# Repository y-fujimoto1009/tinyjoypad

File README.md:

# tinyjoypad キット

tinyjoypad キットは、attiny85を使ったゲーム機を作成するためのキットです。<br>
tinyjoypadプロジェクトは
[こちら](https://www.tinyjoypad.com/tinyjoypad_attiny85) 

## 内容物

- 基板 x 1
- LED x 1
- ピンヘッダー（2×3） x 1
- スライドスイッチ x 1
- attiny85 x 1
- 丸ピンICソケット (8P) x 1
- 抵抗（10kΩ） x 2
- 抵抗（22kΩ） x 2
- 抵抗（33kΩ） x 2
- 抵抗（91kΩ） x 2
- タクトスイッチ x 5
- スイッチキャップ x 5
- ブザー x 1
- ボタン電池ホルダー x 1
- 0.96インチ有機ELディスプレイ(OLED)  x 1
- USBasp AVRライタ x 1(スイッチサイエンスで購入した方のみ）

## 自分で用意する必要があるもの
最近は100均などでも手に入りますね。
- はんだごて、はんだ
- マスキングテープ
- ニッパー
- ボタン電池（CR2032）

## 作成手順
1. 抵抗を基板に書かれた場所に配置します。間違えないようにしましょう。向きは関係ありません。<br>
はんだで接続できたら、余った足はニッパーでカットしてOKです。
どの抵抗かわからなくなっても落ち着いてカラーコードを確認すれば大丈夫です。<br>

<br>
 10kΩ：茶赤黒黒茶<br><br>
 
 22kΩ：赤赤黒赤茶<br><br>
 
 33kΩ：橙橙黒赤茶<br><br>
 
 91kΩ：茶赤黒茶白<br>

2. OLEDを取り付けます。斜めにならないようにマスキングテープなどで固定してからはんだ付けしましょう。<br><br>

3. 電源スイッチを下に向けて取り付けます。ぐらぐらしますので、マスキングテープなどで仮固定してからはんだ付けしましょう。<br><br>

4. タクトスイッチを取り付けます。向きは関係ありません。スイッチキャップも付けましょう。あまり強く押さなくても取り付けられます。<br><br>

5. LEDを取り付けます。足の短い方（カノード）をGNDの方にして取り付けてください。余った足はニッパーでカットしてOKです。<br><br>

6. ピンヘッダ、ICソケットを取り付けます。ICソケットにはattiny85を取り付けます。attiny85は左側にくぼみがくるように取り付けてください。<br><br>

7. ブザーも向きがあります。＋と書いてる方を間違えずに取り付けてください。これで表面は完成です。<br><br>

8. 裏を向けてボタン電池ホルダーを取り付けます。今までと違い表面実装部品なので、先に基板にはんだを少し盛ってから、上から温めて接続するとうまくいきます。<br><br>

あとは電池を＋面が表になるように接続して電源をONにすればゲームが起動するはずです！おめでとう！
起動しない場合ははんだのミス（隣と接続されてしまっている箇所が無いかなど）、attiny85の向き、取付忘れなどないか確認してください。
お問い合わせはk.u.i.f1009@gmail.comまで

## プログラムのインストール手順
初期状態でスペースインベーダーをインストールしていますが、tinyjoypadプロジェクトでは他にも面白いゲームが公開されています。
現状(2024年7月時点）でうまくいったインストール手順を紹介します。

1. [Zadig](https://zadig.akeo.ie/)にアクセスして、Zadigソフトをインストールします。
2. キットについているUSBaspをPCと接続します。
3. Zadigを起動し、USBaspを選択してlibusbkを選択してインストールします。
4. [ArduinoIDE](https://www.arduino.cc/en/software)をインストールします。
5. 基本設定ー＞追加のボードマネージャのURLに次のURLを追加します。https://descartes.net/package_drazzy.com_index.json
6. ツールー＞ボードー＞ボードマネージャの検索欄にattinyと入力してATTinyCore by Spence Kondeのバージョン1.3.2を選択してインストールします。
8. [SSD1306ライブラリ](https://github.com/Defragster/ssd1306xled)をダウンロードし、スケッチー＞ライブラリをインクルードー＞.ZIP形式のライブラリをインストールへと進み、ダウンロードしたzipファイルを選択してインストールを行います。
9. [ゲームデータ](https://github.com/cheungbx/gametiny)をダウンロード、解凍し、好きなゲームの.inoファイルを起動します。
10. ツールー＞ボードー＞ATTinyCoreー＞Attiny25/45/85を選択します。
11. チップはATtiny85、クロックは8MHz(internal)、そして書込装置はUSBaspを選択します。
12. スケッチー＞書き込み装置を使って書き込むを選択します。
13. プログラムが書き込まれます。

詳細な手順やサンプルコードについては、[tinyjoypad](https://www.tinyjoypad.com/tinyjoypad_attiny85)も参照してください。

## 自分で基板を発注してみる
gbrフォルダにあるファイルをJLCPCBなどの基板発注サービスなどに依頼すれば自分で発注することができます。
また、基板データを改造・修正する場合のライセンスはGPLv3です。

## 3Dプリンターでケースを作る
3dmodelフォルダにあるファイルをそのまま3Dプリンターなどで印刷すればケースを付けることができます。M2×15のビスが4本必要です。

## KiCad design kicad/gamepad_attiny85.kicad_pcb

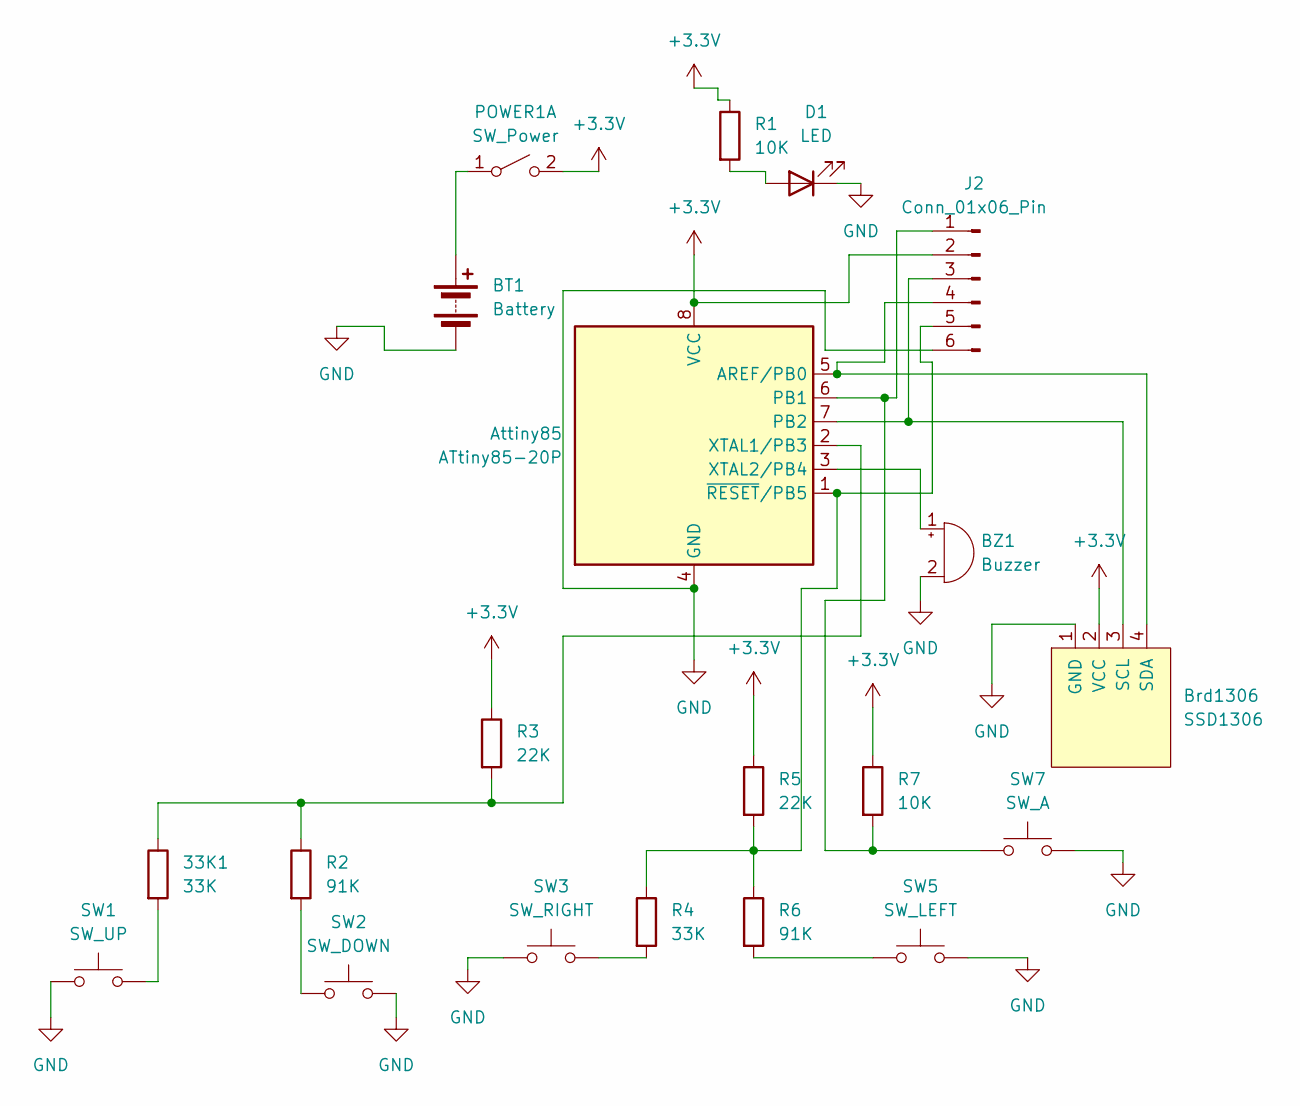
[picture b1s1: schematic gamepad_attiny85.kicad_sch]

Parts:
33K1: 33K; R_Axial_DIN0207_L6.3mm_D2.5mm_P7.62mm_Horizontal
Attiny85: ATtiny85-20P; DIP-8_W7.62mm
BT1: Battery; BatteryHolder_Renata_SMTU2032-LF_1x2032
BZ1: Buzzer; Buzzer_12x9.5RM7.6
Brd1306: SSD1306; 128x64OLED
D1: LED; LED_D3.0mm
J2: Conn_01x06_Pin; PinHeader_2x03_P2.54mm_Vertical
POWER1: SW_Power; SW_Slide_SPDT_Angled_CK_OS102011MA1Q
R1, R7: 10K; R_Axial_DIN0207_L6.3mm_D2.5mm_P7.62mm_Horizontal
R2, R6: 91K; R_Axial_DIN0207_L6.3mm_D2.5mm_P7.62mm_Horizontal
R3, R5: 22K; R_Axial_DIN0207_L6.3mm_D2.5mm_P7.62mm_Horizontal
R4: 33K; R_Axial_DIN0207_L6.3mm_D2.5mm_P7.62mm_Horizontal
SW1: SW_UP; SW_PUSH_6mm_H7.3mm
SW2: SW_DOWN; SW_PUSH_6mm_H7.3mm
SW3: SW_RIGHT; SW_PUSH_6mm_H7.3mm
SW5: SW_LEFT; SW_PUSH_6mm_H7.3mm
SW7: SW_A; SW_PUSH_6mm_H7.3mm

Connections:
+3.3V: Attiny85.8 (VCC), Brd1306.2 (VCC), J2.2, POWER1.2 (B), R1.1, R3.1, R5.1, R7.1
GND: Attiny85.4 (GND), BT1.2 (-), BZ1.2 (+), Brd1306.1 (GND), D1.1 (K), J2.6, SW1.1, SW2.2, SW3.1, SW5.2, SW7.2
unnamed: 33K1.2, SW1.2
unnamed: Attiny85.5 (AREF/PB0), Brd1306.4 (SDA), J2.4
unnamed: Attiny85.6 (PB1), J2.1, R7.2, SW7.1
unnamed: Attiny85.7 (PB2), Brd1306.3 (SCL), J2.3
unnamed: 33K1.1, Attiny85.2 (XTAL1/PB3), R2.1, R3.2
unnamed: Attiny85.3 (XTAL2/PB4), BZ1.1 (-)
unnamed: Attiny85.1 (~RESET/PB5), J2.5, R4.1, R5.2, R6.1
unnamed: BT1.1 (+), POWER1.1 (A)
unnamed: D1.2 (A), R1.2
unnamed: R2.2, SW2.1
unnamed: R4.2, SW3.2
unnamed: R6.2, SW5.1

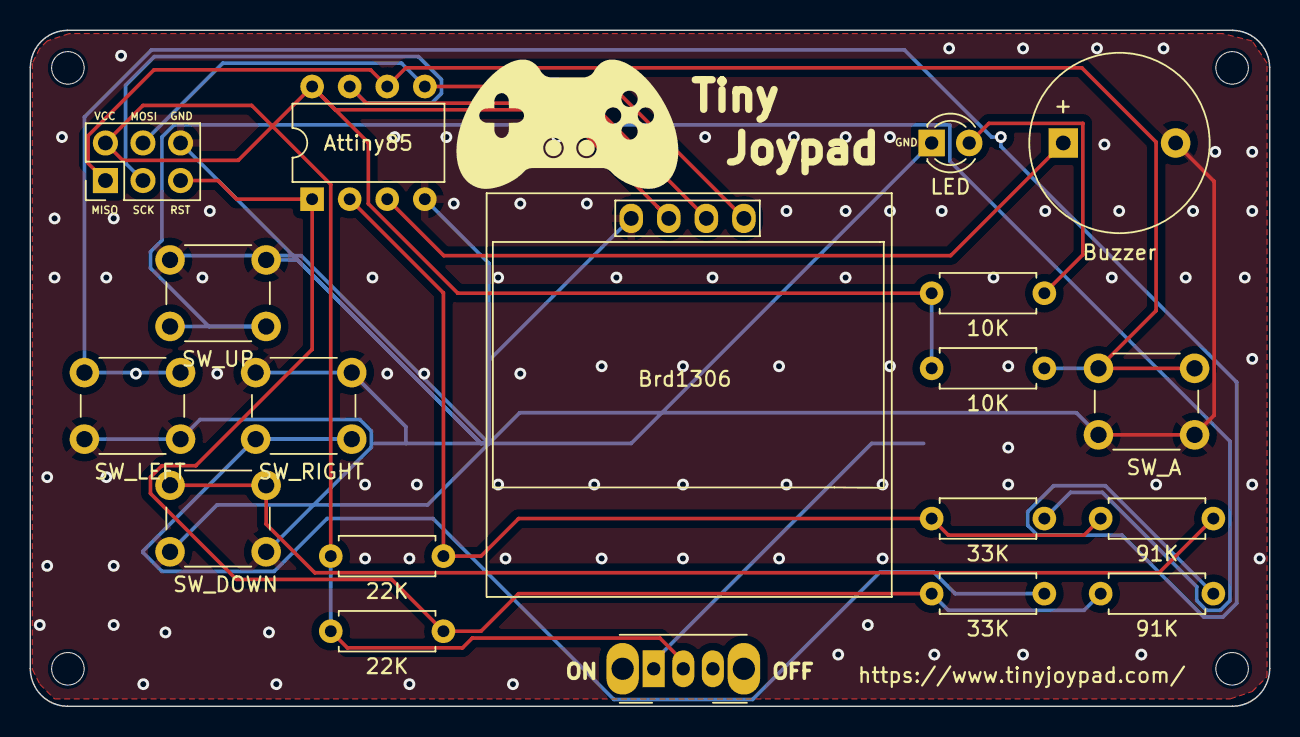
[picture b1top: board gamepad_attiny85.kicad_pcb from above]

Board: 2 copper layers, 83.8 x 45.7 mm, 20 parts (1 on the bottom side), 14 nets.

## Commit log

2024-07-27 file add
